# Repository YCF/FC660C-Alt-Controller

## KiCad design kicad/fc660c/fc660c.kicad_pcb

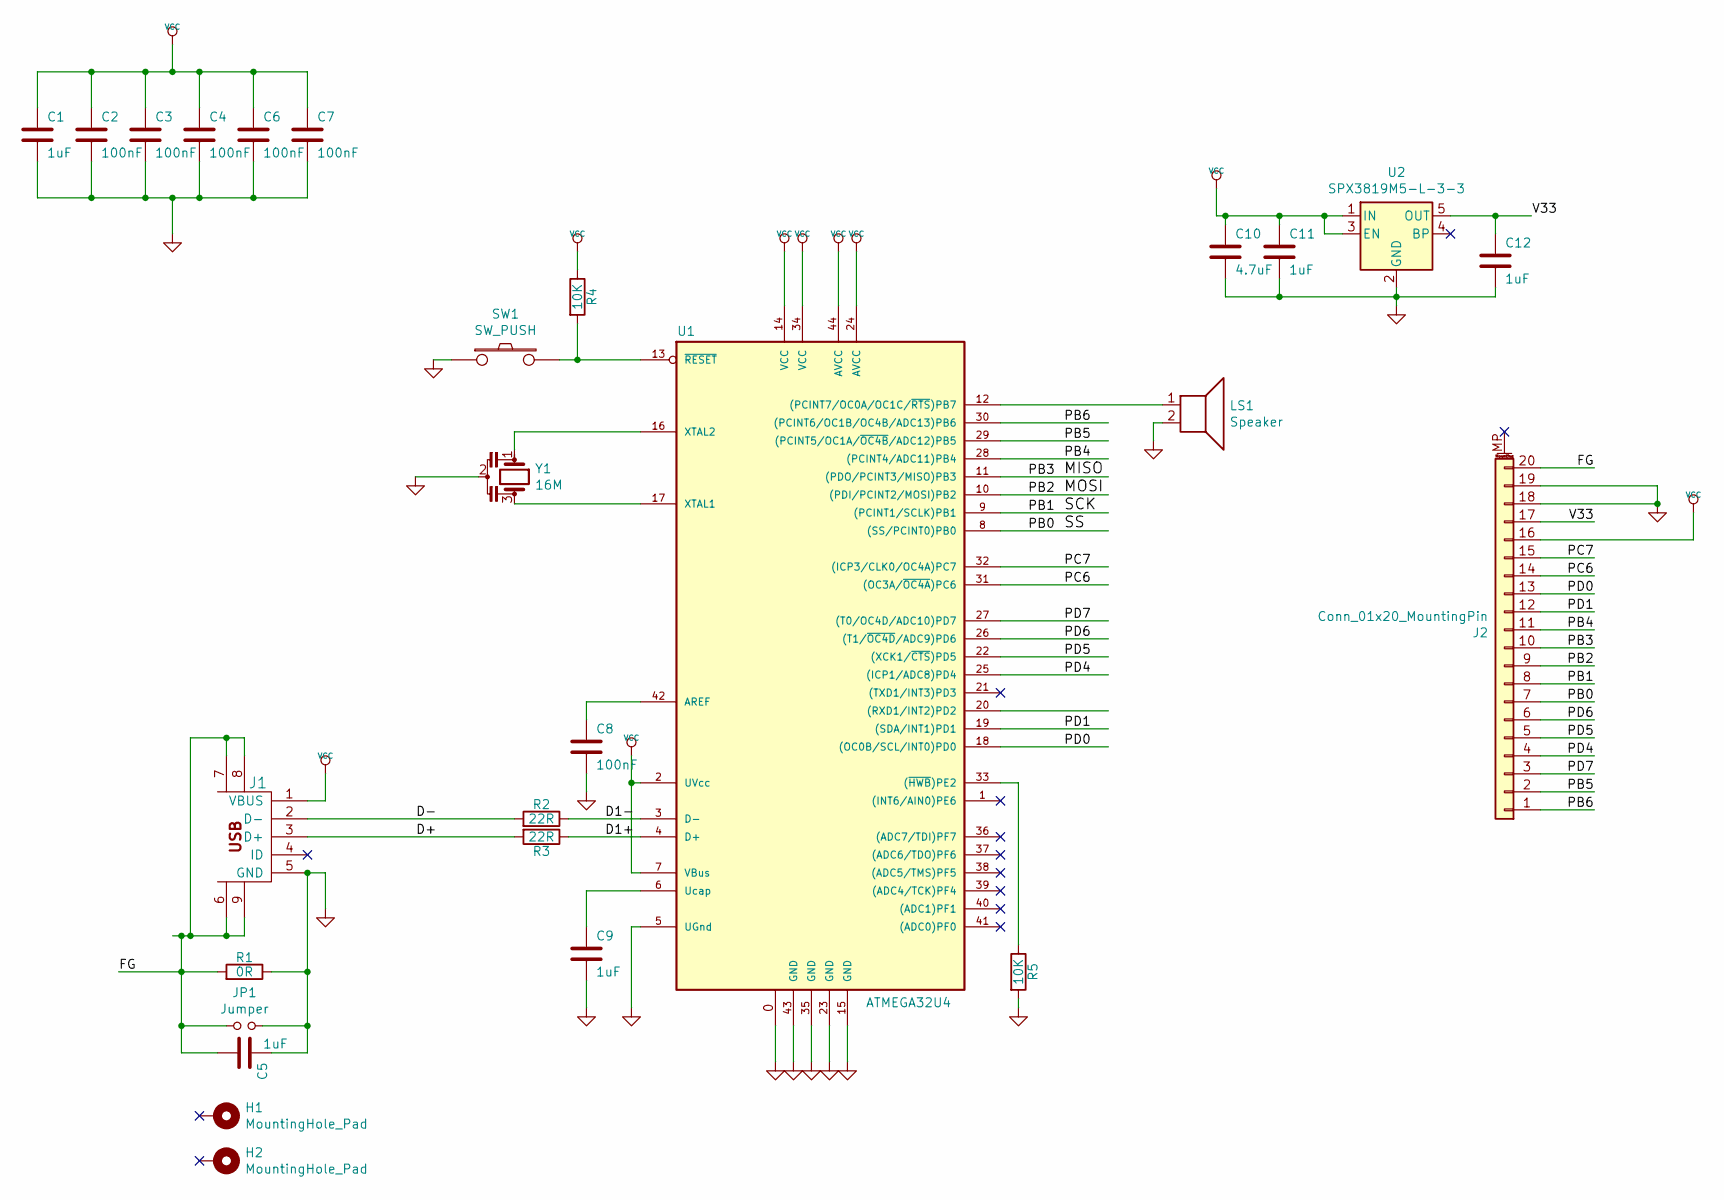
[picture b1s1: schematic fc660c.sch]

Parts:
C1, C5, C9, C11, C12: 1uF; C_0805_2012Metric_Pad1.15x1.40mm_HandSolder
C2, C3, C4, C6, C7, C8: 100nF; C_0805_2012Metric_Pad1.15x1.40mm_HandSolder
C10: 4.7uF; C_1206_3216Metric_Pad1.42x1.75mm_HandSolder
H1, H2: MountingHole_Pad; MountingHole_3.2_long
J1: USB_MINI-B; USB_MINI-B-marked
J2: Conn_01x20_MountingPin; HRS_DF14_20P
JP1: Jumper; SolderJumper-2_P1.3mm_Open_RoundedPad1.0x1.5mm
LS1: Speaker; SPK
R1: 0R; R_0805_2012Metric_Pad1.15x1.40mm_HandSolder
R2, R3: 22R; R_0805_2012Metric_Pad1.15x1.40mm_HandSolder
R4, R5: 10K; R_0805_2012Metric_Pad1.15x1.40mm_HandSolder
SW1: SW_PUSH; SW_Rest
U1: ATMEGA32U4; TQFP44+QFN44
U2: SPX3819M5-L-3-3; SOT-23-5
Y1: 16M; murata-resonator_SMD_CSTCE16M0V53-R0

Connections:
/D1+: R3.1, U1.4 (D+)
/D1-: R2.1, U1.3 (D-)
/D+: J1.3 (D+), R3.2
/D-: J1.2 (D-), R2.2
/FG: C5.2, J1.6, J1.7, J1.8, J1.9, J2.20, JP1.1, R1.2
/MISO: J2.10, U1.11 ((PDO/PCINT3/MISO)PB3)
/MOSI: J2.9, U1.10 ((PDI/PCINT2/MOSI)PB2)
/PB0: J2.7, U1.8 ((SS/PCINT0)PB0)
/PB1: J2.8, U1.9 ((PCINT1/SCLK)PB1)
/PB4: J2.11, U1.28 ((PCINT4/ADC11)PB4)
/PB5: J2.2, U1.29 ((PCINT5/OC1A/~OC4B~/ADC12)PB5)
/PB6: J2.1, U1.30 ((PCINT6/OC1B/OC4B/ADC13)PB6)
/PC6: J2.14, U1.31 ((OC3A/~OC4A~)PC6)
/PC7: J2.15, U1.32 ((ICP3/CLK0/OC4A)PC7)
/PD0: J2.13, U1.18 ((OC0B/SCL/INT0)PD0)
/PD1: J2.12, U1.19 ((SDA/INT1)PD1)
/PD4: J2.4, U1.25 ((ICP1/ADC8)PD4)
/PD5: J2.5, U1.22 ((XCK1/~CTS~)PD5)
/PD6: J2.6, U1.26 ((T1/~OC4D~/ADC9)PD6)
/PD7: J2.3, U1.27 ((T0/OC4D/ADC10)PD7)
/V33: C12.1, J2.17, U2.5 (OUT)
GND: C1.2, C2.2, C3.2, C4.2, C5.1, C6.2, C7.2, C8.2, C9.2, C10.2, C11.2, C12.2, J1.5 (GND), J2.18, J2.19, JP1.2, LS1.2, R1.1, R5.2, SW1.1, U1.0, U1.5 (UGnd), U1.15 (GND), U1.23 (GND), U1.35 (GND), U1.43 (GND), U2.2 (GND), Y1.2
unnamed: C8.1, U1.42 (AREF)
unnamed: C9.1, U1.6 (Ucap)
unnamed: LS1.1, U1.12 ((PCINT7/OC0A/OC1C/~RTS~)PB7)
unnamed: R4.2, SW1.2, U1.13 (~RESET~)
unnamed: R5.1, U1.33 ((~HWB~)PE2)
unnamed: U1.16 (XTAL2), Y1.1
unnamed: U1.17 (XTAL1), Y1.3
VCC: C1.1, C2.1, C3.1, C4.1, C6.1, C7.1, C10.1, C11.1, J1.1 (VBUS), J2.16, R4.1, U1.2 (UVcc), U1.7 (VBus), U1.14 (VCC), U1.24 (AVCC), U1.34 (VCC), U1.44 (AVCC), U2.1 (IN), U2.3 (EN)

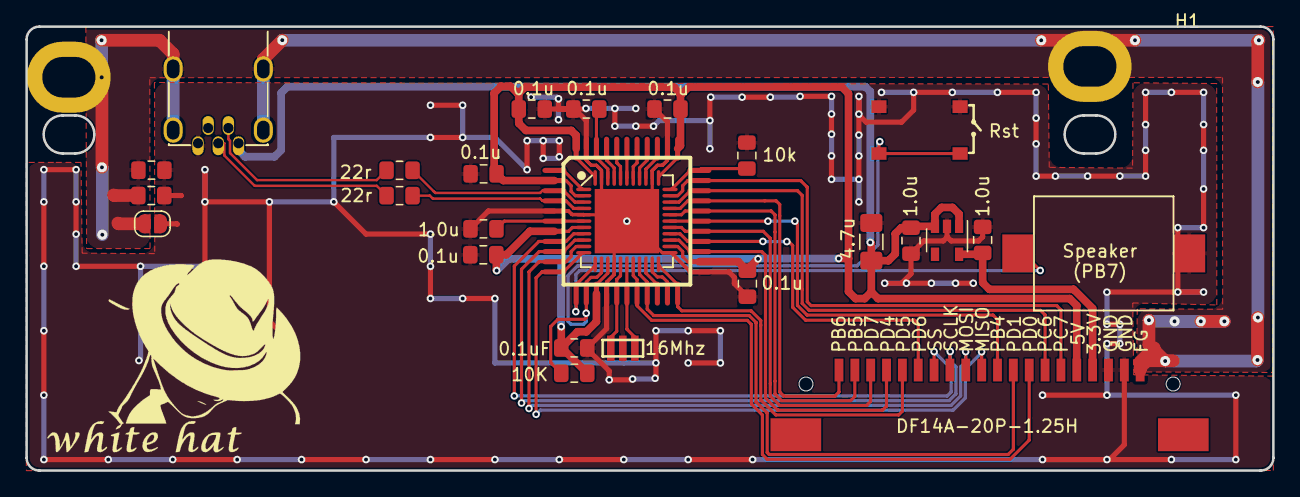
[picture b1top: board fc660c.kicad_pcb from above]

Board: 2 copper layers, 98.3 x 35.0 mm, 27 parts (0 on the bottom side), 30 nets.

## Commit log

2019-03-09 rev.A
2019-03-17 Add QMK FIrmware
